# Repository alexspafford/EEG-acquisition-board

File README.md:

# EEG-acquisition-board
All design files for an EEG acquisition board

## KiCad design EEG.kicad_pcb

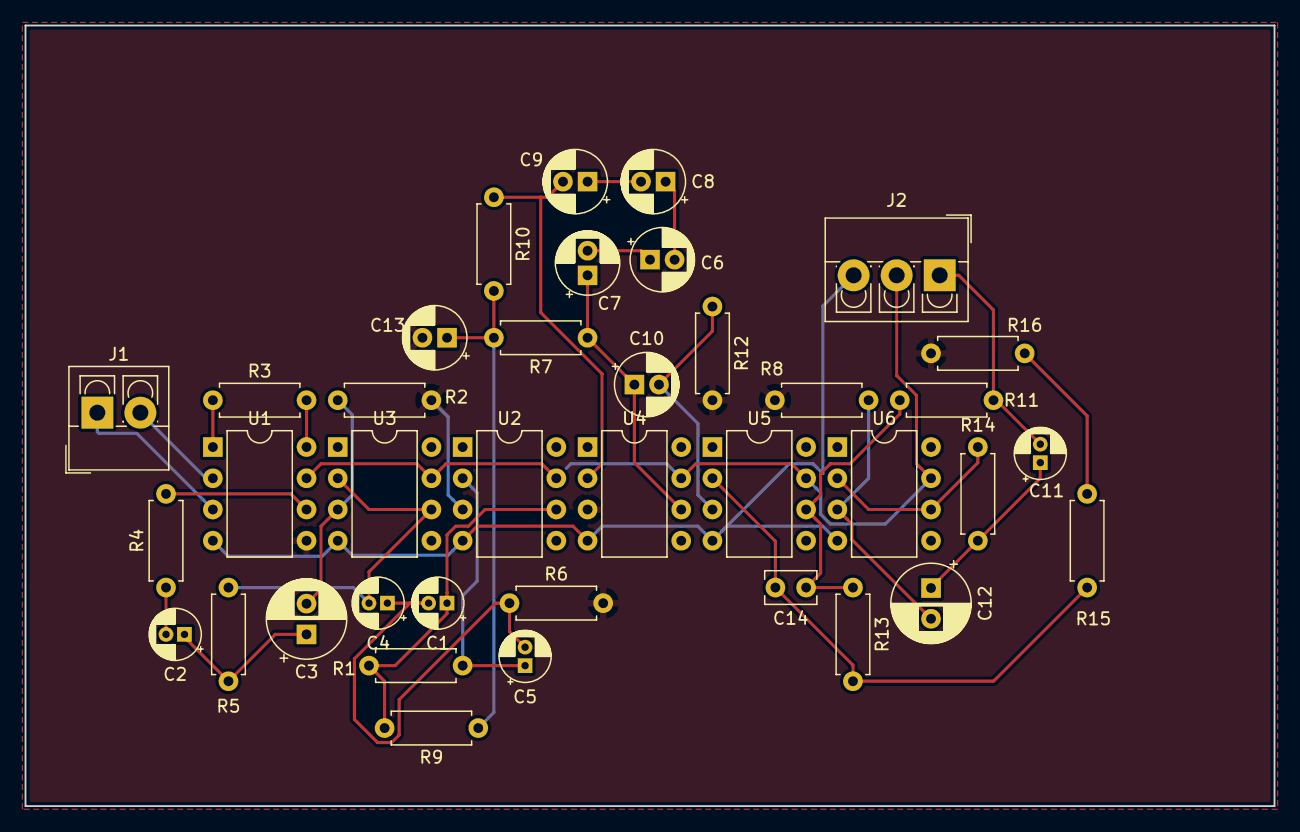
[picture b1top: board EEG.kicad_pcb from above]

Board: 2 copper layers, 101.6 x 63.5 mm, 38 parts (0 on the bottom side), 29 nets.

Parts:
C1, C2, C4, C5, C11: 220n; CP_Radial_D4.0mm_P1.50mm
C3, C12: 10u; CP_Radial_D6.3mm_P2.50mm
C6, C7, C8, C9: 0.1u; CP_Radial_D5.0mm_P2.00mm
C10: 1u; CP_Radial_D5.0mm_P2.00mm
C13: 100n; CP_Radial_D5.0mm_P2.00mm
C14: 10n; C_Rect_L4.0mm_W2.5mm_P2.50mm
J1: Screw_Terminal_01x02; TerminalBlock_4Ucon_1x02_P3.50mm_Vertical
J2: Screw_Terminal_01x03; TerminalBlock_4Ucon_1x03_P3.50mm_Vertical
R1, R15: 220k; R_Axial_DIN0207_L6.3mm_D2.5mm_P7.62mm_Horizontal
R2, R8: 270k; R_Axial_DIN0207_L6.3mm_D2.5mm_P7.62mm_Horizontal
R3: 560; R_Axial_DIN0207_L6.3mm_D2.5mm_P7.62mm_Horizontal
R4, R11: 22k; R_Axial_DIN0207_L6.3mm_D2.5mm_P7.62mm_Horizontal
R5, R14: 12; R_Axial_DIN0207_L6.3mm_D2.5mm_P7.62mm_Horizontal
R6: 47k; R_Axial_DIN0207_L6.3mm_D2.5mm_P7.62mm_Horizontal
R7, R9: 180k; R_Axial_DIN0207_L6.3mm_D2.5mm_P7.62mm_Horizontal
R10, R13: 100k; R_Axial_DIN0207_L6.3mm_D2.5mm_P7.62mm_Horizontal
R12: 1M; R_Axial_DIN0207_L6.3mm_D2.5mm_P7.62mm_Horizontal
R16: 1k; R_Axial_DIN0207_L6.3mm_D2.5mm_P7.62mm_Horizontal
U1: AD620; DIP-8_W7.62mm
U2, U3, U4, U5, U6: LM741; DIP-8_W7.62mm

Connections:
+9V: J2.2, U1.7, U2.7, U3.7, U4.7, U5.7, U6.7
-9V: J2.3, U1.4, U2.4, U3.4, U4.4, U5.4, U6.4
GND: C13.2, R2.1, R6.2, R8.1, R12.2, R16.2, U1.5, U2.3, U4.3
unnamed: C1.1, R1.1, R9.2, U2.6
unnamed: C1.2, C4.1, C5.2, R6.1
unnamed: C2.1, C3.1, R5.1
unnamed: C2.2, R4.1
unnamed: C3.2, R2.2, U3.3
unnamed: C4.2, R5.2, U3.2, U3.6
unnamed: C5.1, R1.2, U2.2
unnamed: C6.1, C7.2
unnamed: C6.2, C8.1
unnamed: C8.2, C9.1
unnamed: C9.2, R10.1, U4.2
unnamed: C7.1, C10.1, R7.1, U4.6
unnamed: C10.2, R12.1, U5.3
unnamed: C11.1, C12.1, R14.2
unnamed: C11.2, J2.1, R11.1
unnamed: C12.2, R8.2, U6.3
unnamed: C13.1, R7.2, R9.1, R10.2
unnamed: C14.1, R11.2, R13.1, U5.6
unnamed: C14.2, R13.2, R15.1, U5.2
unnamed: J1.1, U1.3
unnamed: J1.2, U1.2
unnamed: R3.1, U1.1
unnamed: R3.2, U1.8
unnamed: R4.2, U1.6
unnamed: R14.1, U6.2, U6.6
unnamed: R15.2, R16.1

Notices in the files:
EEG.kicad_pcb:
License: CC BY 4.0
